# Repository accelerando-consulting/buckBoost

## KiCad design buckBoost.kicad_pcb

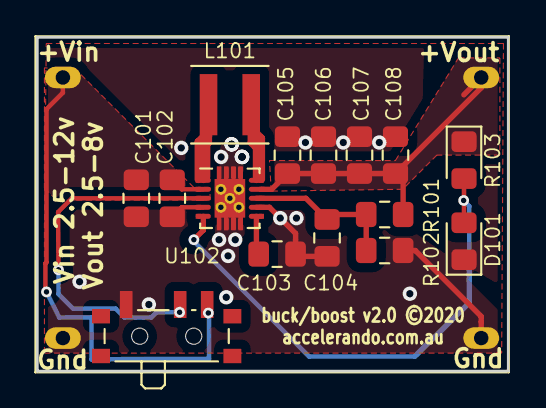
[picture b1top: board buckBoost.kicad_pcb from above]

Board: 2 copper layers, 26.2 x 18.5 mm, 16 parts (0 on the bottom side), 9 nets.

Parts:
C101, C102, C105, C106, C107: 10u; C_0805_2012Metric_Pad1.15x1.40mm_HandSolder
C103: 0.1u; C_0805_2012Metric_Pad1.15x1.40mm_HandSolder
C104: 10p; C_0805_2012Metric_Pad1.15x1.40mm_HandSolder
C108: C; C_0805_2012Metric_Pad1.15x1.40mm_HandSolder
D101: LED; D_0805_2012Metric_Pad1.15x1.40mm_HandSolder
L101: LPS4020-152; L_Coilcraft_XxL4020
R101: 1M; R_0805_2012Metric_Pad1.15x1.40mm_HandSolder
R102: 180k; R_0805_2012Metric_Pad1.15x1.40mm_HandSolder
R103: 1k; D_0805_2012Metric_Pad1.15x1.40mm_HandSolder
SW1: PWRON; SW_SPDT_PCM12
U101: BUCKBOOST
U102: TPS63060; Texas_S-PWSON-N10_ThermalVias

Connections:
+BATT: C101.1, C102.1, SW1.3, U101.1, U102.2
/EN: SW1.2, U102.3
/FB: C104.1, R101.2, R102.1, U102.8
/L1: L101.1, U102.1
/L2: L101.2, U102.10
/PG: D101.2, R103.2, U102.5
/VAUX: C103.1, U102.6
GND: C101.2, C102.2, C103.2, C104.2, C105.2, C106.2, C107.2, C108.2, D101.1, R102.2, SW1.1, U101.2, U101.3, U102.4, U102.7, U102.11
VCC: C105.1, C106.1, C107.1, C108.1, R101.1, R103.1, U101.4, U102.9

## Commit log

2022-05-24 a versatile buck-boost power module
2022-05-24 Kicad version bump (6.0.4)
2024-05-22 V2 adds a power switch

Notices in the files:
buckBoost.kicad_pcb:
buck/boost v2.0 ©2020
